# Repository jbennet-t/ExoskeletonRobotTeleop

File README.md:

# ExoskeletonRobotTeleop
Project centered around development of a wearable exoskeleton that translates user joint positions and movements in real time to a humanoid NAO robot.
Developed by Jordan Sinoway and Brian Dawson for 2021 Senior Capstone Project @ TCNJ

Exoskeleton embedded and Python code developed for Teensy 3.5 and NAO v4 robot, however could easily be reapplied to a new microcontroller and robot. Would suggest not using the NAO in the future due to reliability issues. 

This project is free to build and improve upon.

If you have any questions about the project, feel free to contact me.

## Exoskeleton Overview Model

## Abstract
The goal of this project is to create a novel exoskeleton apparatus that captures the movements of the wearer, and then translates these movements to a humanoid robot, granting approximately real-time teleoperation. The robot utilized for this project is Aldebaran Robotics’ NAO, a ⅓ scale humanoid robot. Teleoperation has many practical applications, including hazardous waste disposal, robotics surgery, and tasks in the military, space, sea, and medical sectors. Potentiometers are integrated into the mechanical design at key joints in the wrist, elbow, and shoulder of the exoskeleton. These sensors vary their voltage depending on the joint angle and these values are passed to the Teensy 3.5 microcontroller via a 13-bit ADC. The microcontroller then converts the data into usable angle measurements and passes them to a Python layer, via a serial data line, which in turn converts the angle measurements into commands the robot can interpret. The embedded code in the microcontroller is written in C++ and the Python intermediary layer utilizes Python 2.7 and the NAOqi SDK to control the robot. 

### What's Important
- Python_Intermediary_Layer.py - https://github.com/jbennet-t/ExoskeletonRobotTeleop/blob/master/Brian-Code/Python_Intermediary_Layer.py
- Everything in the Diagrams subdirectory
- Exoskeleton_main.ino https://github.com/jbennet-t/ExoskeletonRobotTeleop/blob/master/EmbeddedCode/exoskeleton_main/exoskeleton_main.ino
- Everything in the Exoskeleton_Models subdirectory (all stls are not up to date, should be regenerated)
- Exoskeleton_PCBv3: https://github.com/jbennet-t/ExoskeletonRobotTeleop/tree/master/PCB/Exoskeleton_PCBv3

### Materials List
Items required: (Approximate Cost ~$250)
- Teensy 3.5 Microcontroller (x1)
- Bourns PDF241-S425F Potentiometers (x12)
- STM LD1117 3.3V Fixed Voltage Regulator (x1)
- 3-Terminal Might-SPOX Molex Male Header (x12)
- 3-Terminal Might-SPOX Molex Female Header (x12)
- Film Capacitors (x3)
- Green Through-hole LED (x1)
- 2 Pole Switch (x1)
- M5 Bolts and Nuts (x20)
- 12ft USB 2.0 Cable (x1)
- ¾” PVC Pipe - 4ft Segment (x5)
- Backpack Straps (x2)
- 22 AWG Silicone Wire 40ft (x1)
- 3D Printed Components
- Printed Circuit Board
- Power Supply
- Laptop

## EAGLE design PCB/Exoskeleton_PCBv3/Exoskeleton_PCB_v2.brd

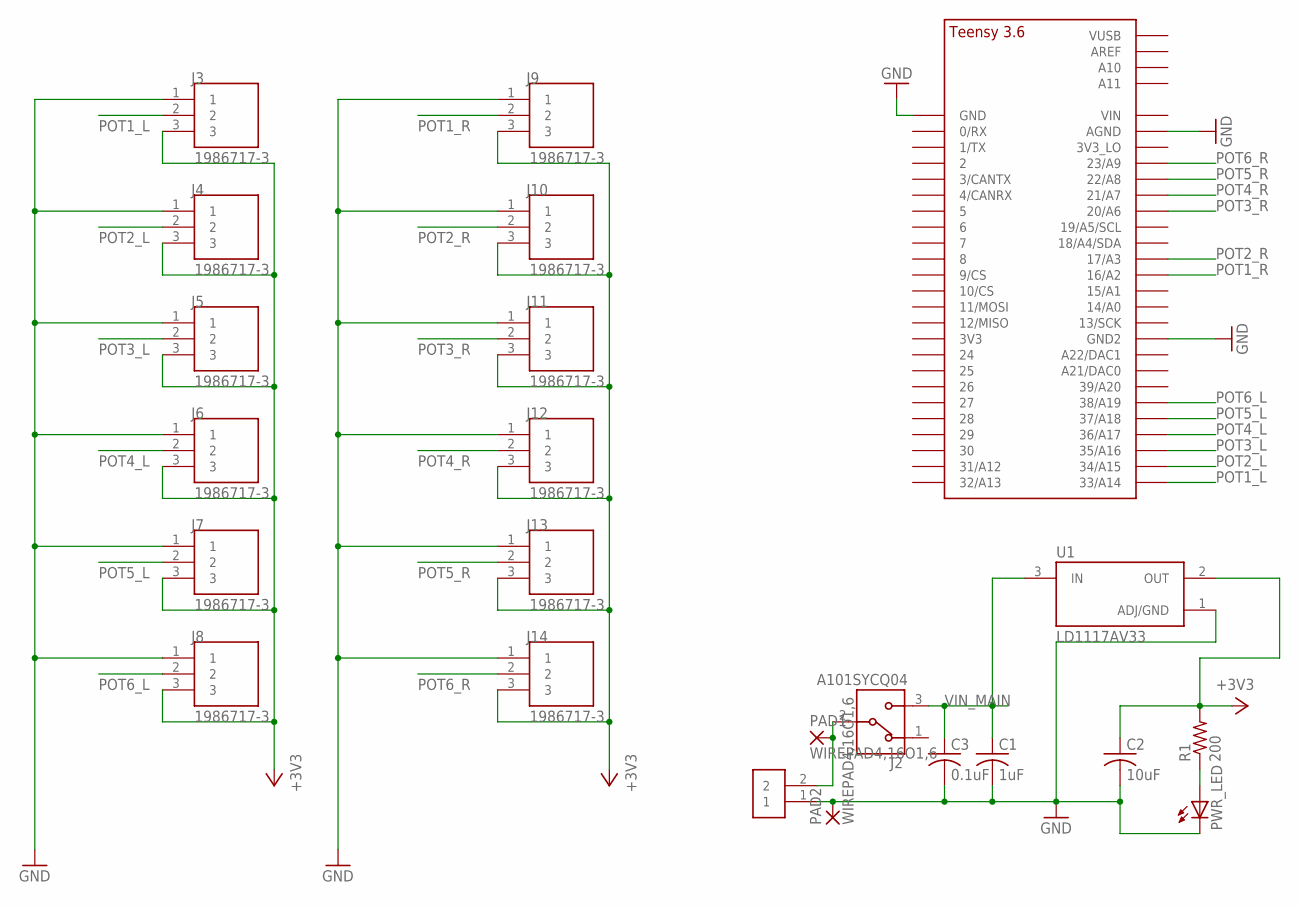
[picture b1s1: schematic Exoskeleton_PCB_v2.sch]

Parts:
C1: 1uF; C050-030X075
C2: 10uF; C050-030X075
C3: 0.1uF; C050-030X075
J1: 282837-2; TE_282837-2
J2: A101SYCQ04; TE_A101SYCQ04
J3, J4, J5, J6, J7, J8, J9, J10, J11, J12, J13, J14: 1986717-3; TE_1986717-3
PAD1, PAD2: WIREPAD4,16O1,6; 4,16O1,6
PWR_LED: LED5MM
R1: 200; 0207/9
U1: LD1117AV33; TO255P1020X450X1968-3
U$1: TEENSY_3.5/3.6_BASIC

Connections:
+3V3: C2.1, J3.3, J4.3, J5.3, J6.3, J7.3, J8.3, J9.3, J10.3, J11.3, J12.3, J13.3, J14.3, R1.2, U1.2 (OUT)
GND: C1.2, C2.2, C3.2, J1.1, J3.1, J4.1, J5.1, J6.1, J7.1, J8.1, J9.1, J10.1, J11.1, J12.1, J13.1, J14.1, PAD2.1, PWR_LED.K (C), U1.1 (ADJ/GND), U$1.AGND, U$1.GND, U$1.GND2
unnamed: PWR_LED.A, R1.1
unnamed: J1.2, J2.2, PAD1.1
POT1_L: J3.2, U$1.33/A14
POT1_R: J9.2, U$1.16/A2
POT2_L: J4.2, U$1.34/A15
POT2_R: J10.2, U$1.17/A3
POT3_L: J5.2, U$1.35/A16
POT3_R: J11.2, U$1.20/A6
POT4_L: J6.2, U$1.36/A17
POT4_R: J12.2, U$1.21/A7
POT5_L: J7.2, U$1.37/A18
POT5_R: J13.2, U$1.22/A8
POT6_L: J8.2, U$1.38/A19
POT6_R: J14.2, U$1.23/A9
VIN_MAIN: C1.1, C3.1, J2.3, U1.3 (IN)

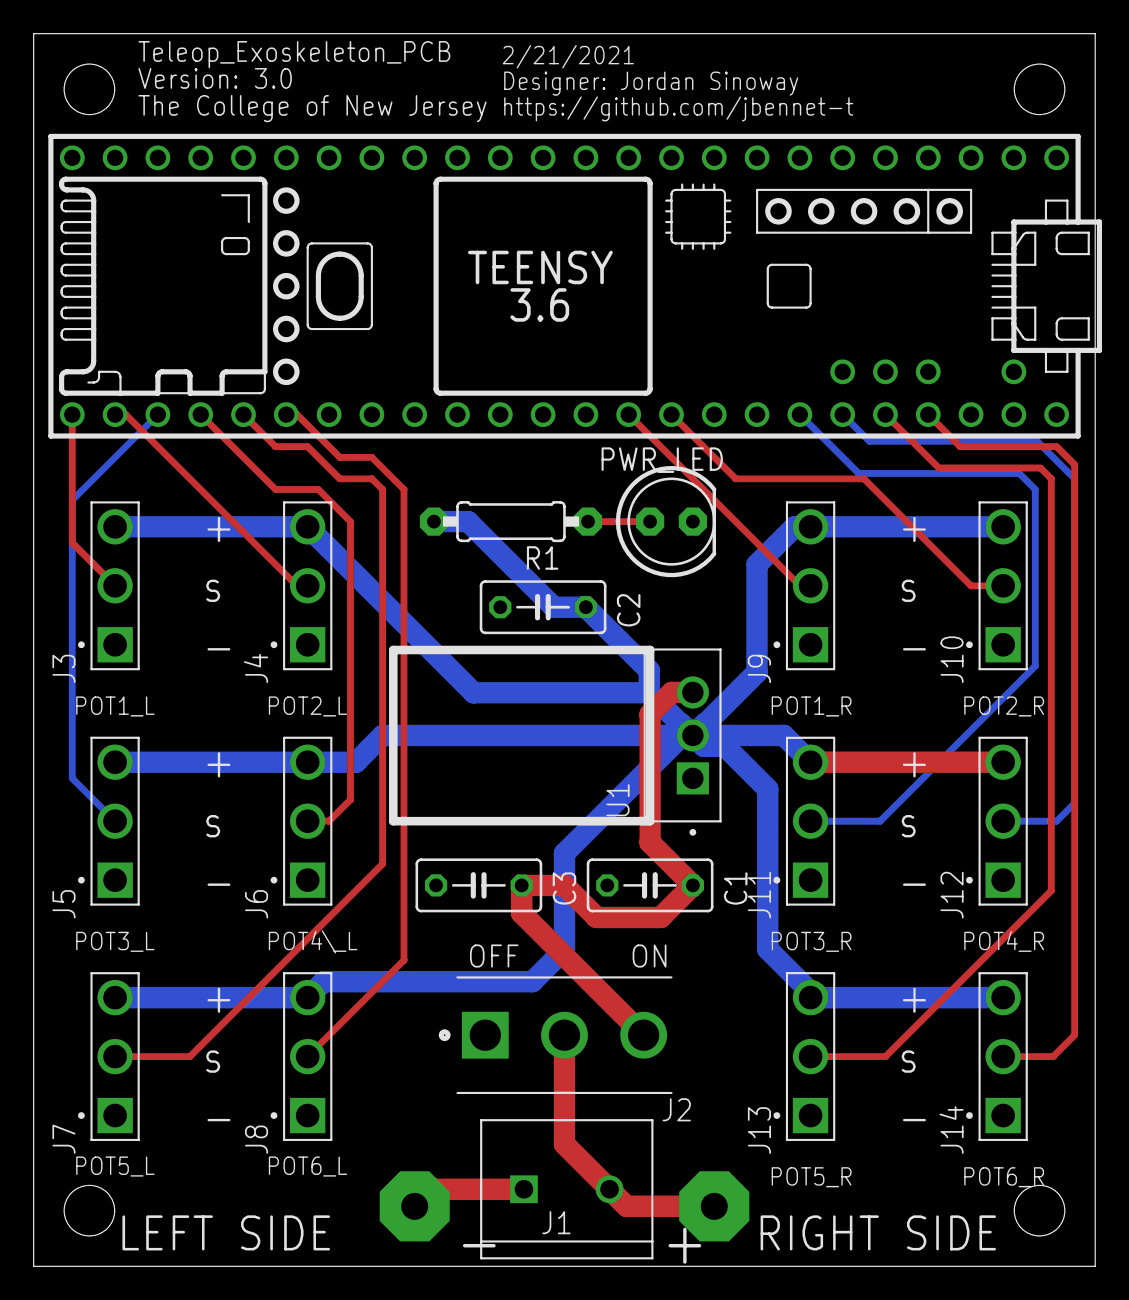
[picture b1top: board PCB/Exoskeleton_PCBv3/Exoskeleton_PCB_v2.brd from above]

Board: 2 copper layers, 63.0 x 73.2 mm, 23 parts (0 on the bottom side), 17 nets.

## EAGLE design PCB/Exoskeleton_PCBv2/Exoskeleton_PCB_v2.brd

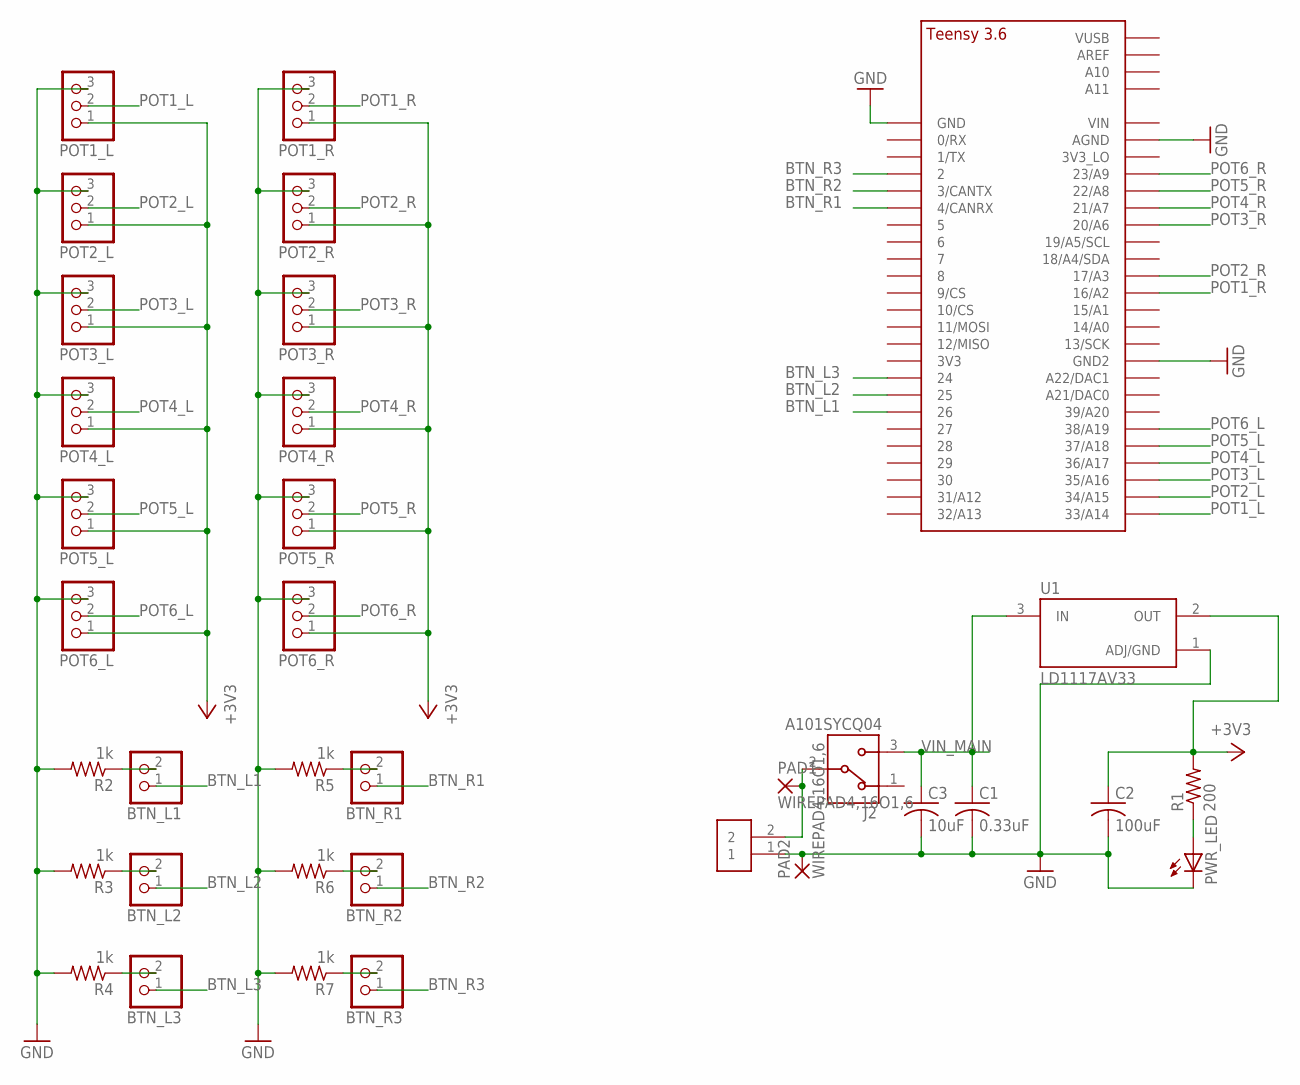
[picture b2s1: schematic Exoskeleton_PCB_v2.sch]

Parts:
BTN_L1, BTN_L2, BTN_L3: PINHD-1X2; 1X02
BTN_R1, BTN_R2, BTN_R3: PINHD-1X2; 1X02
C1: 0.33uF; C050-030X075
C2: 100uF; C050-030X075
C3: 10uF; C050-030X075
J1: 282837-2; TE_282837-2
J2: A101SYCQ04; TE_A101SYCQ04
PAD1, PAD2: WIREPAD4,16O1,6; 4,16O1,6
POT1_L, POT1_R, POT2_L, POT2_R, POT3_L, POT3_R, POT4_L, POT4_R, POT5_L, POT5_R, POT6_L, POT6_R: PINHD-1X3; 1X03
PWR_LED: LED5MM
R1: 200; 0207/9
R2, R3, R4, R5, R6, R7: 1k; 0207/9
U1: LD1117AV33; TO255P1020X450X1968-3
U$1: TEENSY_3.5/3.6_BASIC

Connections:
+3V3: C2.1, POT1_L.1, POT1_R.1, POT2_L.1, POT2_R.1, POT3_L.1, POT3_R.1, POT4_L.1, POT4_R.1, POT5_L.1, POT5_R.1, POT6_L.1, POT6_R.1, R1.2, U1.2 (OUT)
BTN_L1: BTN_L1.1, U$1.26
BTN_L2: BTN_L2.1, U$1.25
BTN_L3: BTN_L3.1, U$1.24
BTN_R1: BTN_R1.1, U$1.4/CANRX
BTN_R2: BTN_R2.1, U$1.3/CANTX
BTN_R3: BTN_R3.1, U$1.2
GND: C1.2, C2.2, C3.2, J1.1, PAD2.1, POT1_L.3, POT1_R.3, POT2_L.3, POT2_R.3, POT3_L.3, POT3_R.3, POT4_L.3, POT4_R.3, POT5_L.3, POT5_R.3, POT6_L.3, POT6_R.3, PWR_LED.K (C), R2.2, R3.2, R4.2, R5.2, R6.2, R7.2, U1.1 (ADJ/GND), U$1.AGND, U$1.GND, U$1.GND2
unnamed: PWR_LED.A, R1.1
unnamed: BTN_L1.2, R2.1
unnamed: BTN_L3.2, R4.1
unnamed: BTN_L2.2, R3.1
unnamed: BTN_R1.2, R5.1
unnamed: BTN_R2.2, R6.1
unnamed: BTN_R3.2, R7.1
unnamed: J1.2, J2.2, PAD1.1
POT1_L: POT1_L.2, U$1.33/A14
POT1_R: POT1_R.2, U$1.16/A2
POT2_L: POT2_L.2, U$1.34/A15
POT2_R: POT2_R.2, U$1.17/A3
POT3_L: POT3_L.2, U$1.35/A16
POT3_R: POT3_R.2, U$1.20/A6
POT4_L: POT4_L.2, U$1.36/A17
POT4_R: POT4_R.2, U$1.21/A7
POT5_L: POT5_L.2, U$1.37/A18
POT5_R: POT5_R.2, U$1.22/A8
POT6_L: POT6_L.2, U$1.38/A19
POT6_R: POT6_R.2, U$1.23/A9
VIN_MAIN: C1.1, C3.1, J2.3, U1.3 (IN)

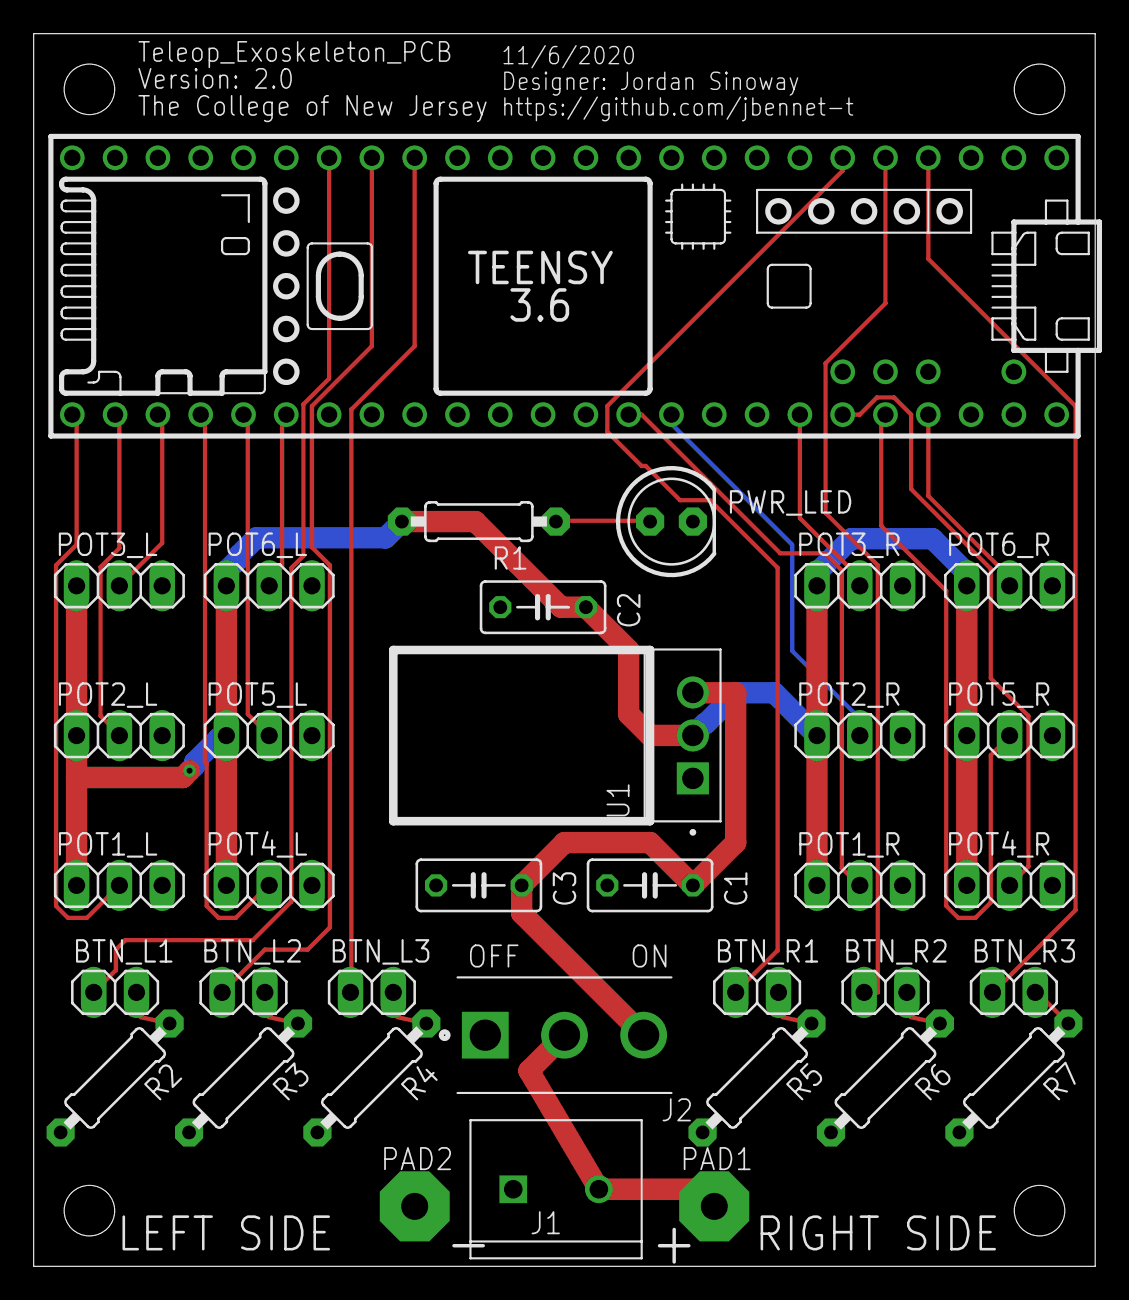
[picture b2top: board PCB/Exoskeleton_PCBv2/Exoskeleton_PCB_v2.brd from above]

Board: 2 copper layers, 63.0 x 73.2 mm, 35 parts (0 on the bottom side), 29 nets.

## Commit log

2020-08-28 adding pic and folders
2020-10-25 Added python code for robot
2020-10-25 added PCB directory, CAD directory, embedded code, python code
2020-10-28 Added serial logic
2020-11-06 probably fixed first try at getting serial working, added embbeded code
2020-11-08 updated exoskeleton_main
2020-11-10 Fixed serial code and added error catching
2020-11-10 Added comments and cleaned up code
2020-11-25 updated python code
2020-11-25 updated embedded code
2021-02-07 Adjusted code
2021-02-10 updated testing.py
2021-02-17 created new file for joint testing
2021-02-17 added start up sequence
2021-03-10 added right arm to embedded, some changes to python
2021-04-07 updating python and embedded code to current working version
2021-04-07 ruh roh
2021-04-07 Made formatting of threading nicer
2021-04-29 April 2021 updates, finalized
2021-04-29 Create LICENSE
